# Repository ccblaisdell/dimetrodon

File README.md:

# Dimetrodon
A 36 key split keyboard with stagger and splay, built with Ergogen.

## Images
| Top | Bottom |
| --- | --- |
|  |  |

## Development

- Clone the git repository.
- Install NodeJS.
- Run `npm install`.
- Run `make build`.

## Acknowledgements

- Ergogen
- Rae-dux
- Totem
- FlatFootFox
- linalinn/kicad-render
- Scottokeebs

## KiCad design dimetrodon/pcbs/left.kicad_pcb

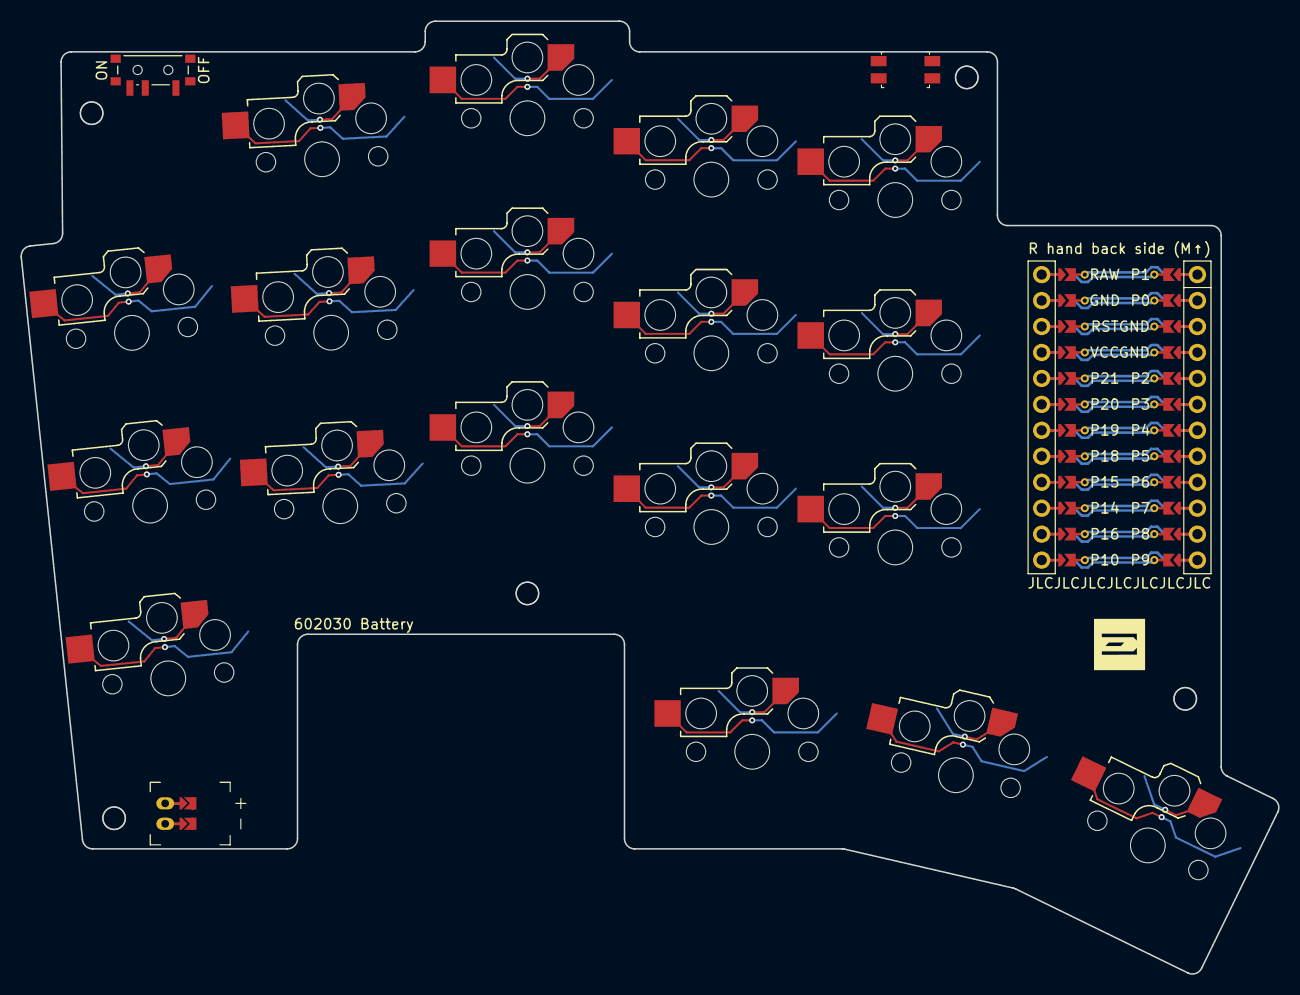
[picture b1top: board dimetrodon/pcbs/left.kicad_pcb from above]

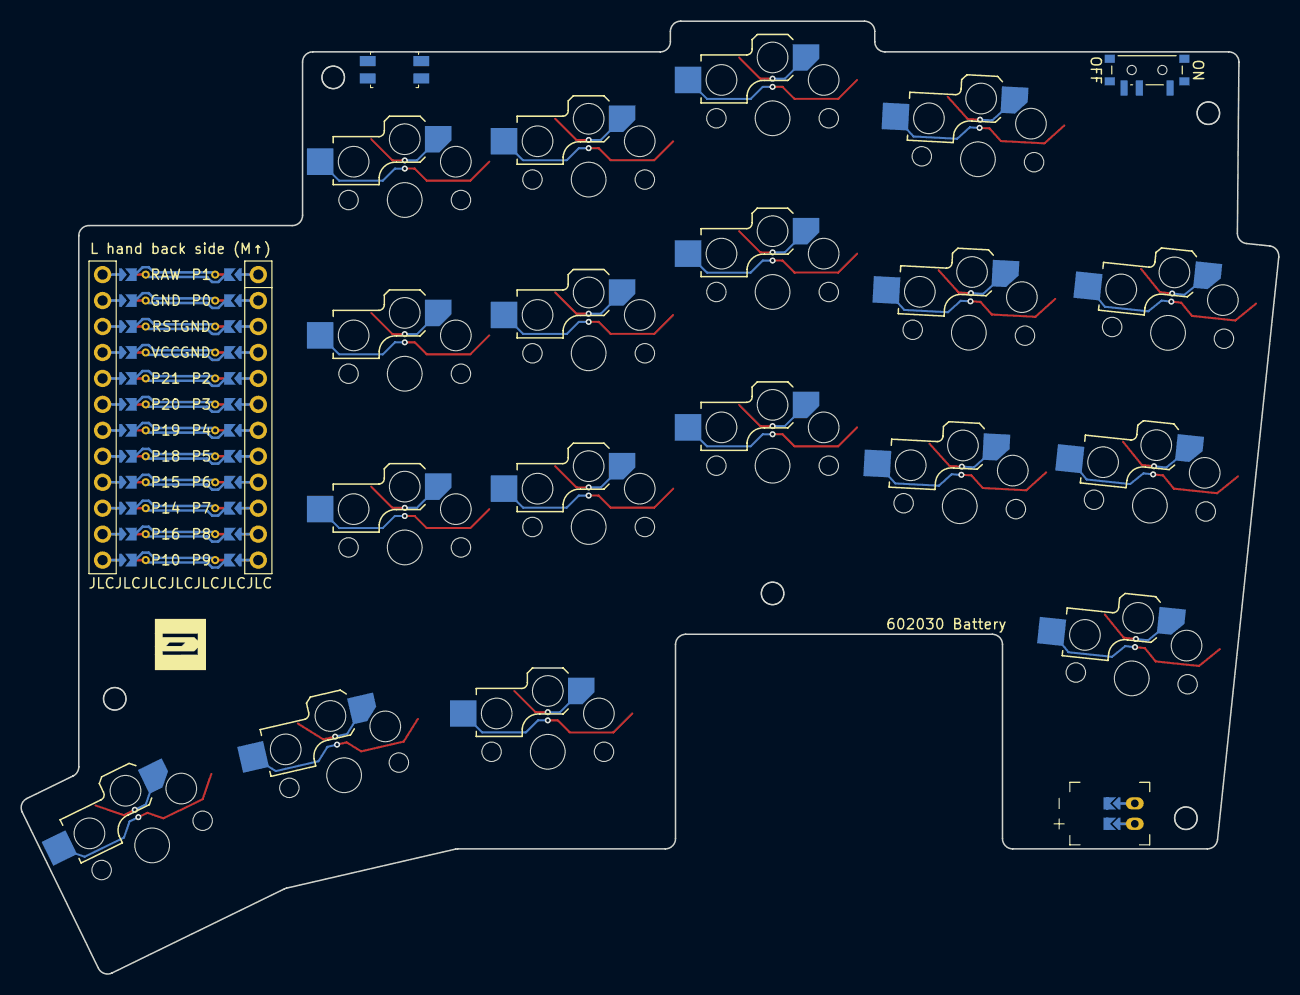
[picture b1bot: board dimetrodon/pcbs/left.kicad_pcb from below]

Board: 2 copper layers, 123.1 x 93.2 mm, 28 parts (18 on the bottom side), 24 nets.

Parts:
JST1: battery_connector_jst_ph_2
LOGO1: utility_ergogen_logo
MCU1: mcu_nice_nano
MH1, MH2, MH3, MH4, MH5: mounting_hole_npth
PWR1: power_switch_smd_side
RST1: reset_switch_smd_side
S1, S2, S3, S4, S5, S6, S7, S8, S9, S10, S11, S12, S13, S14, S15, S16, S17, S18: switch_choc_v1_v2

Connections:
Braw: JST1.1, PWR1.1, PWR1.3
GND: JST1.2, MCU1.103, MCU1.104, MCU1.123, RST1.1, RST1.3, S1.2, S2.2, S3.2, S4.2, S5.2, S6.2, S7.2, S8.2, S9.2, S10.2, S11.2, S12.2, S13.2, S14.2, S15.2, S16.2, S17.2, S18.2
JST1_1: JST1.11, JST1.21, JST1.31
JST1_2: JST1.12, JST1.22, JST1.32
P0: MCU1.102, S14.1
P1: MCU1.101, S15.1
P2: MCU1.105, S13.1
P3: MCU1.106, S12.1
P4: MCU1.107, S11.1
P5: MCU1.108, S10.1
P6: MCU1.109, S9.1
P7: MCU1.110, S8.1
P8: MCU1.111, S7.1
P9: MCU1.112, S6.1
P10: MCU1.113, S5.1
P14: MCU1.115, S3.1
P15: MCU1.116, S2.1
P16: MCU1.114, S4.1
P18: MCU1.117, S1.1
P19: MCU1.118, S16.1
P20: MCU1.119, S17.1
P21: MCU1.120, S18.1
RAW: MCU1.124, PWR1.2
RST: MCU1.122, RST1.2, RST1.4

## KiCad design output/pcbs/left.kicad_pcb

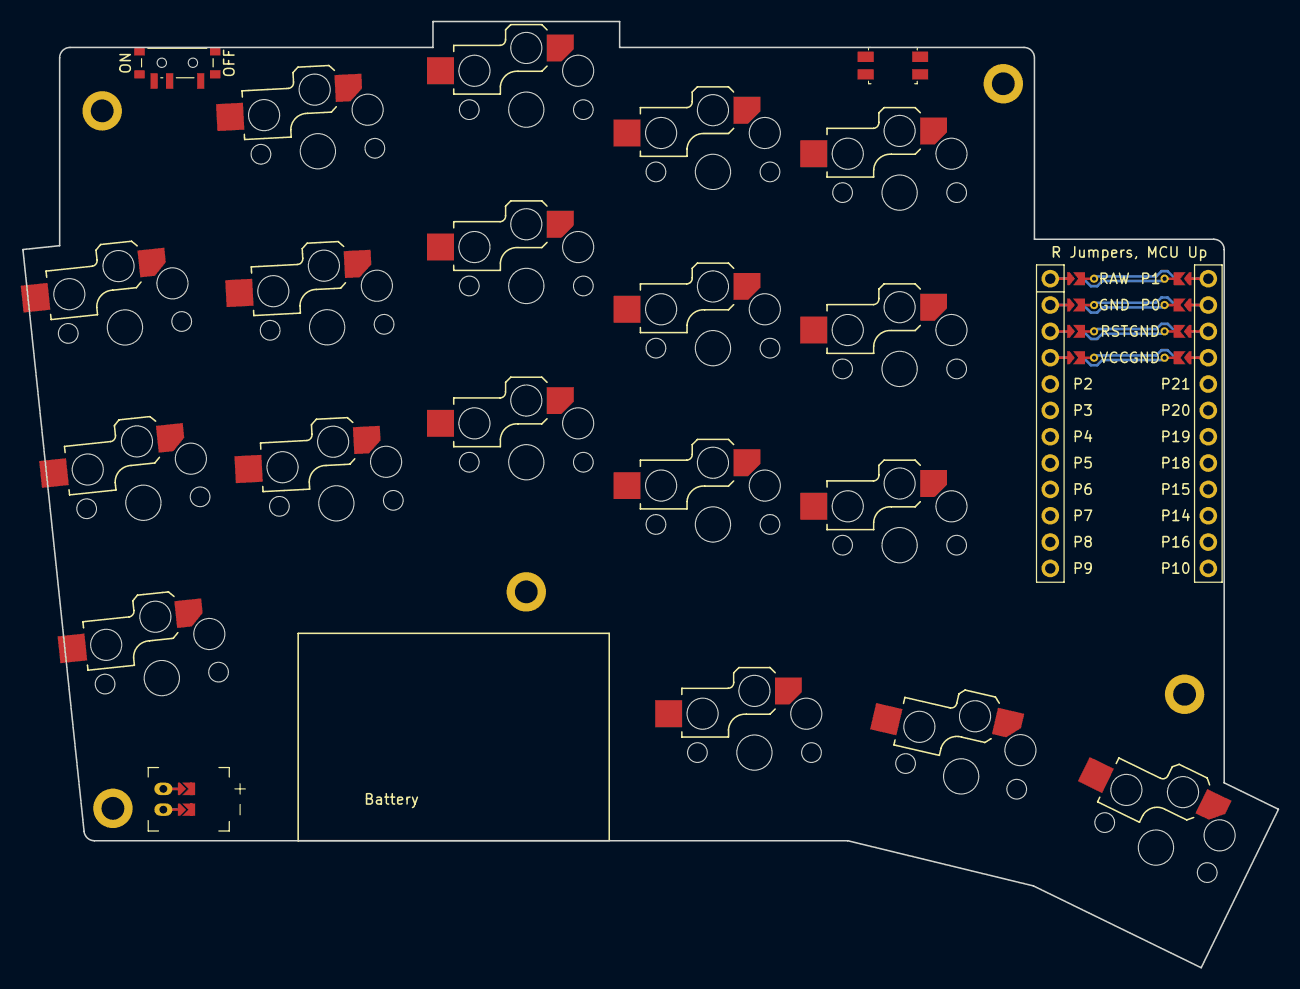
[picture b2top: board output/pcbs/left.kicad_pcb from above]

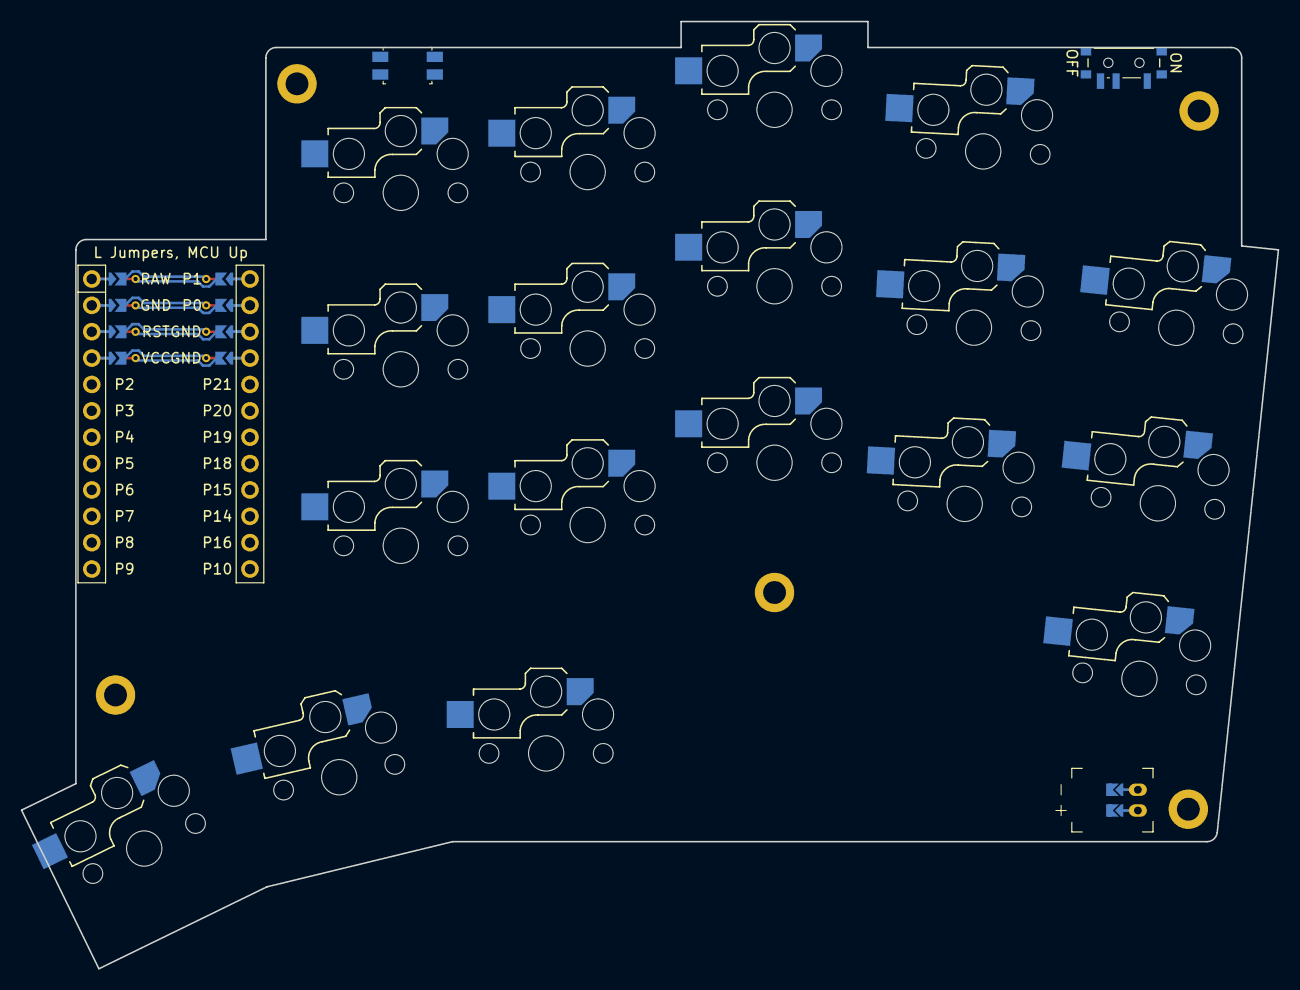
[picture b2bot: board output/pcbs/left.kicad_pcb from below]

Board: 2 copper layers, 121.1 x 91.2 mm, 27 parts (18 on the bottom side), 24 nets.

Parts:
H1, H2, H3, H4, H5: mounting_hole_plated
JST1: battery_connector_jst_ph_2
MCU1: mcu_nice_nano
PWR1: power_switch_smd_side
RST1: reset_switch_smd_side
S1, S2, S3, S4, S5, S6, S7, S8, S9, S10, S11, S12, S13, S14, S15, S16, S17, S18: switch_choc_v1_v2

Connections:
Braw: JST1.1, PWR1.1, PWR1.3
GND: JST1.2, MCU1.103, MCU1.104, MCU1.123, RST1.1, RST1.3, S1.2, S2.2, S3.2, S4.2, S5.2, S6.2, S7.2, S8.2, S9.2, S10.2, S11.2, S12.2, S13.2, S14.2, S15.2, S16.2, S17.2, S18.2
JST1_1: JST1.11, JST1.21, JST1.31
JST1_2: JST1.12, JST1.22, JST1.32
P0: MCU1.102, S14.1
P1: MCU1.101, S15.1
P2: MCU1.20, S13.1
P3: MCU1.19, S12.1
P4: MCU1.18, S11.1
P5: MCU1.17, S10.1
P6: MCU1.16, S9.1
P7: MCU1.15, S8.1
P8: MCU1.14, S7.1
P9: MCU1.13, S6.1
P10: MCU1.12, S5.1
P14: MCU1.10, S3.1
P15: MCU1.9, S2.1
P16: MCU1.11, S4.1
P18: MCU1.8, S1.1
P19: MCU1.7, S16.1
P20: MCU1.6, S17.1
P21: MCU1.5, S18.1
RAW: MCU1.124, PWR1.2
RST: MCU1.122, RST1.2, RST1.4

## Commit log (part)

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2024-11-16 Rename to dimetrodon
2024-11-16 Add first version of config file, following along with:
    https://flatfootfox.com/ergogen-part1-units-points/
2024-11-17 Add basic outlines
    Not sure if any of these will actually be used, but they're handy for visualizing the progress of the board so far.
2024-11-17 Add ergogen package
    init npm toolchain and add ergogen
    also add gitignore
2024-11-17 Add makefile and build instructions
2024-11-17 Add initial PCB definition
    I haven't previewed it yet in Kicad, so I have
    no idea if it's any good.
2024-11-17 Try generating images on github
    add github action from https://github.com/linalinn/kicad-render
    check in output files
    still need to run the build in GHA
2024-11-17 Fix path to pcb
2024-11-17 Fix path to pcb 2
2024-11-17 Fix image paths in readme
2024-11-17 Put images into a table
2024-11-17 Put images into a table 2
2024-11-17 Tuck thumbs up a little higher and 4mm out
2024-11-18 Add ceoloide footprints
2024-11-18 Add models for choc and nano
2024-11-18 Remove ergogen workflow
2024-11-18 Add pre-commit hook to run the build
2024-11-18 Try to move MCU into place
2024-11-18 Reset MCU y placement just to see
2024-11-18 Shift MCU down 30mm
2024-11-18 Shift MCU around a little more
    -1 ky, and raise up the 3d model just for the preview
2024-11-18 More gentle tweaking
2024-11-18 Undo reversibleness and mirror the sides
2024-11-18 Spacing
2024-11-18 Spread the splayed cols
2024-11-18 Move the nice nano
2024-11-18 Make a switch plate outline
2024-11-19 Working on a better PCB outline
2024-11-19 Cut a shrink-wrapped cheapino-style pcb
2024-11-19 Scoot the controller up
2024-11-19 Draw MCU outline
2024-11-19 Add PCB back for MCU
2024-11-19 Make most outlines private
2024-11-19 Splay thumbs out more
2024-11-19 Add JST connector
2024-11-19 Add preview outline with battery and JST connector
2024-11-19 Clean up preview a bit more
2024-11-19 Extend board under palm to hold battery and connector
2024-11-19 Turn off 3d models in preview
2024-11-19 Add debug rectangle to locate power, reset switches
2024-11-19 Move power/reset switches, draw battery guide
2024-11-19 Try drawing battery on User layer
2024-11-19 Try drawing battery on F.Silkscreen layer
2024-11-19 Try drawing battery on F.SilkS layer
2024-11-19 Remove debug rect, add outlines to position reset/power switches
2024-11-19 Add top left part to board
2024-11-19 Try to line up power/reset switches with their outlines
2024-11-19 Reposition little components
2024-11-19 Adjust placement of switches
2024-11-19 Adjust horizontally
2024-11-19 Adjust power/reset a little more
2024-11-19 Add mounting holes
2024-11-19 Shift JST
2024-11-19 Use references to place components
2024-11-20 Add battery text
2024-11-20 Use rae-dux style routing config
    for the choc switch footprint and the nice nano
    footprint. I'm using footprints from ceocloide,
    but copying config from Andrew J Rae:
    https://github.com/andrewjrae/rae-dux-v2/blob/development/config.yaml
2024-11-20 Set up nets for components
2024-11-20 Customize MCU labels
2024-11-20 Move battery text the correct direction
2024-11-20 Reset pin labels
2024-11-20 Reuse JST outline for component
2024-11-20 Position JST more robustly
    also tuck thumbs up a little more
2024-11-20 Make jst pcb and outline behave better
2024-11-20 Tweaking jst outline+component
2024-11-20 Try to share placement of controller outline + component
2024-11-20 Fix bad math on controller outline
2024-11-20 shift the MCU way up
2024-11-20 Fix controller length
2024-11-20 Tweak power switch a little more:
2024-11-21 Fix column nets
2024-11-21 Remove expand from thumb fan outline
2024-11-21 Remove expand from keywell
2024-11-22 Notes
2024-11-22 Use intersect fn to get bottom corner
2024-11-22 Make all components reversible
2024-11-22 Only required jumpers for the nice nano
    Most of them can be reversed in firmware
2024-11-22 Added todo for autorouting
2024-11-22 Restore all jumpers for mcu
2024-11-22 More notes
2024-11-22 Restructure
2024-11-22 Add kibot action to gen images, gerbers
2024-11-22 Fix route for the old image generator
2024-11-22 Upload images to pages and fix pcb file ref
2024-11-22 Upload images and gerbers too
2024-11-22 Wait for build before deploying pages
2024-11-22 Change kibot output directories
2024-11-22 Change out images and remove old generator
2024-11-22 Export DSN for freerouting
2024-11-22 Autoroute PCB
2024-11-22 Import SES
2024-11-22 Generate images, gerbers for autorouted board
2024-11-22 Fix paths to actions
2024-11-22 Make kibot python scripts executable
2024-11-22 Fix another action path
2024-11-22 Add 0.5mm between switch footprint and edge
2024-11-22 Add tons of expands
2024-11-23 Add filled zone
2024-11-23 Remove temporary expands and move power switch slightly away from the edge
2024-11-23 Convert most key-relative measures back to cpx/y
2024-11-23 Add 1mm padding to edge
2024-11-23 Cut out battery area
2024-11-23 Actually cut the battery area out of the PCB
2024-11-23 Try to make a smaller filled zone
2024-11-23 Manually complete routes
2024-11-23 Create cases for easier prototyping
2024-11-23 Only run ergogen on commit
2024-11-24 Start on an actual case
2024-11-24 Cut out jst, reset, power from switch plate
2024-11-24 Fix little wrinkle on left edge
2024-11-24 Use 3d models in ergogen config, export STEP of pcb and components
2024-11-24 Add model for reset switch
2024-11-24 Center the pcb STEP file
2024-11-24 Add debug expand to bottom left outline
2024-11-24 Add a little extra padding to the matrix
2024-11-24 Get rid of unneeded controller area outline
2024-11-25 Expand controller cover by 0.5, still not sure where errors are coming from
2024-11-25 Remove a point from thumbs to see if it repairs the pcb
2024-11-25 Revert some changes to _top_left outline
2024-11-25 Revert "Revert some changes to _top_left outline"
    This reverts commit d7e42cc0c0f2e5e38a55a1e65a7b5e1e25547955.
2024-11-25 Revert "Remove a point from thumbs to see if it repairs the pcb"
    This reverts commit 76eb0660dbf51346b92fff85e03e4c57a7b0377b.
2024-11-25 Revert "Expand controller cover by 0.5, still not sure where errors are coming from"
    This reverts commit ebd9cb7d8961ba2d2a77d8516babe68063261386.
2024-11-25 Revert "Get rid of unneeded controller area outline"
    This reverts commit 3796ed55db745c662bb00451b6e183e0dd8cdd61.
2024-11-25 Revert "Add a little extra padding to the matrix"
    This reverts commit b05fdf7d1df92123cfa0b6a0201ea7a5b458c5c9.
2024-11-25 Revert "Add debug expand to bottom left outline"
    This reverts commit 2952a1b36b20894c5beac89090488edbac0d4e22.
2024-11-25 Revert "Center the pcb STEP file"
    This reverts commit 9bfe07c6180ff07f22c52da49f05be7d0127aca9.
2024-11-25 Revert "Add model for JST connector:"
    This reverts commit 7e076f3fa477bc9f8390b1e38d0062841e01c502.
2024-11-25 Revert "Add model for reset switch"
    This reverts commit 44c92c9fbd36959947cab02473343d2d28c2e747.
2024-11-25 Revert "Fix little wrinkle on left edge"
    This reverts commit cdaa560e3bb4de96c661b7d1fbcadd1cc05848b6.
2024-11-25 Revert "Cut out jst, reset, power from switch plate"
    This reverts commit bf11300e2549d54ba0bd4d4421eb3121b2451d5a.
2024-11-25 Add unused courtyard outlines for reset, power, and JST
2024-11-25 Make controller more narrow, _top_left wider to cover it
2024-11-25 Subtract mounting holes from base and pcb outlines
2024-11-25 Remove top two mounting holes
2024-11-25 Remove bottom middle hole
2024-11-25 Remove bottom right hole
2024-11-25 Remove bottom left hole
2024-11-25 Restore holes except bottom left
2024-11-25 Remove mounting holes
2024-11-25 Adjust how far middle finger sticks out from the top
    shooting in the dark to try and fix this edge issue
2024-11-25 Remove kicad shift to debug outline coordinates
2024-11-25 Restore 'controller_area' outline
    controller_cover now subtracts from this. the area outline will
    be used in pcb and other outlines that are actually functional,
    and cover will just be used for the case.
2024-11-25 Restore the top left mounting hole. Hope it works!
2024-11-25 Disable copper fill to see if it fixes the hole issues
2024-11-25 Restore copper fill
2024-11-25 Remove expand on controller cover
2024-11-25 Restore kicad origin translation
2024-11-25 Try switching to non-plated mounting hole
2024-11-25 Change all holes to non plated
2024-11-25 Try a better wiring setup, maybe its more solvable
2024-11-25 Swap around a few pin assignments
2024-11-26 Wire rows first instead of cols first
2024-11-26 Revert "Wire rows first instead of cols first"
    This reverts commit 3c4794044432473890ef1c2f8a1e804d3262da1d.
2024-11-26 Revert "Swap around a few pin assignments"
    This reverts commit 49207986db77539a4d281e71b42a971c91786d55.
2024-11-26 Revert "Try a better wiring setup, maybe its more solvable"
    This reverts commit 779ee643710634eb545d8b17a1ea1ffac16ddf0a.
2024-11-26 Update manually routed pcb and export model
2024-11-27 Remove all filleting
    will need to add this back in for the PCB, but the filleting
    is weird on some of the outlines, so will need to add them
    back in piecemeal.
    Also added tags to the keys and notes for making a Point-
    centric config.
2024-11-27 Set up empty points, convert mcu to point
2024-11-27 Play a little w xiao controller
2024-11-27 Convert reset switch to a point
2024-11-27 Convert JST to a point
2024-11-27 Rename _jst outline to _jst_connector
2024-11-27 Convert battery to a point
2024-11-27 Convert top left corner to a point
2024-11-28 Convert top right corner to a point
    Also make both top left and top right points intersections
    with the top of the keyboard and the top corner key.
2024-11-28 Make bottom left corner a point
2024-11-28 Convert all mounting holes to points
2024-11-28 Convert several polygon outlines to rectangles
2024-11-28 Redefine several areas in relation to new points
2024-11-28 Make MCU positioning and cover more robust
2024-11-28 Make mcu cover bottom an arc!
2024-11-28 Define thumb fan radius in KXs
2024-11-28 Make mcu connection to thumb fan a little more robust
2024-11-29 Fix optical alignment between jst outline and footprint
2024-11-29 Add 1mm padding to edge again
2024-11-29 Fix rotation of switch and hotswap models for left hand
2024-12-02 Move back to ceoloide footprints
    for JST and reset switch
2024-12-02 Double checking viability of footprints with models
2024-12-02 Copy footprints in
2024-12-02 Copy in footprint fixes
2024-12-02 Use infused kims reset switch model
2024-12-02 Use infused kims models where possible
2024-12-02 Add ergogen logo and JLC order num
2024-12-02 #7 Add left edge to thumb fan case
2024-12-04 Convert left edge of thumb fan case to points
2024-12-06 Add model for single hotswap, for use in creating a cutout footprint
2024-12-06 Update PCB 3d model
2024-12-10 Update battery label
2024-12-13 Add tenting puck, need to test in KiCad
2024-12-13 Shift puck down and try rotating it
2024-12-13 Move tenting puck a little towards pointer
2024-12-13 Dial it in
2024-12-14 Manually route the latest version:
2025-01-16 Remove tenting puck
    Let's just get this thing ordered! Maybe I'll add support in v2
2025-01-16 Updated PCB, but this is still WIP
2025-01-16 Remove infused kim footprints
2025-01-16 Clean up submodules and re-add ceoloide footprints
2025-01-16 Add all 3d models back into PCB file
    re-added infused kim footprints, the source of some of
    the 3d models. Uncommented model config in ergogen yml.
    Regenerated PCB
2025-01-17 Update the 3d model
2025-01-17 Update routes
2025-01-17 Generate gerbers and images from manually routed board
2025-01-18 Make 3d model have a 1.2mm thick PCB
2025-02-15 Update config.yaml
    Copying in changes from the local ergogen window.
    I need to manually reconcile this with other unsaved
    changes on the mac side,
2025-02-17 Add left and right base outlines with cutouts
2025-02-17 Try to use upgrade upload pages artifacts
2025-02-17 Add DXF npm package for converting DXF to svg
2025-02-19 Added dxf-to-svg npm script to be used later
2025-02-19 Dialing in the cutouts for the base
